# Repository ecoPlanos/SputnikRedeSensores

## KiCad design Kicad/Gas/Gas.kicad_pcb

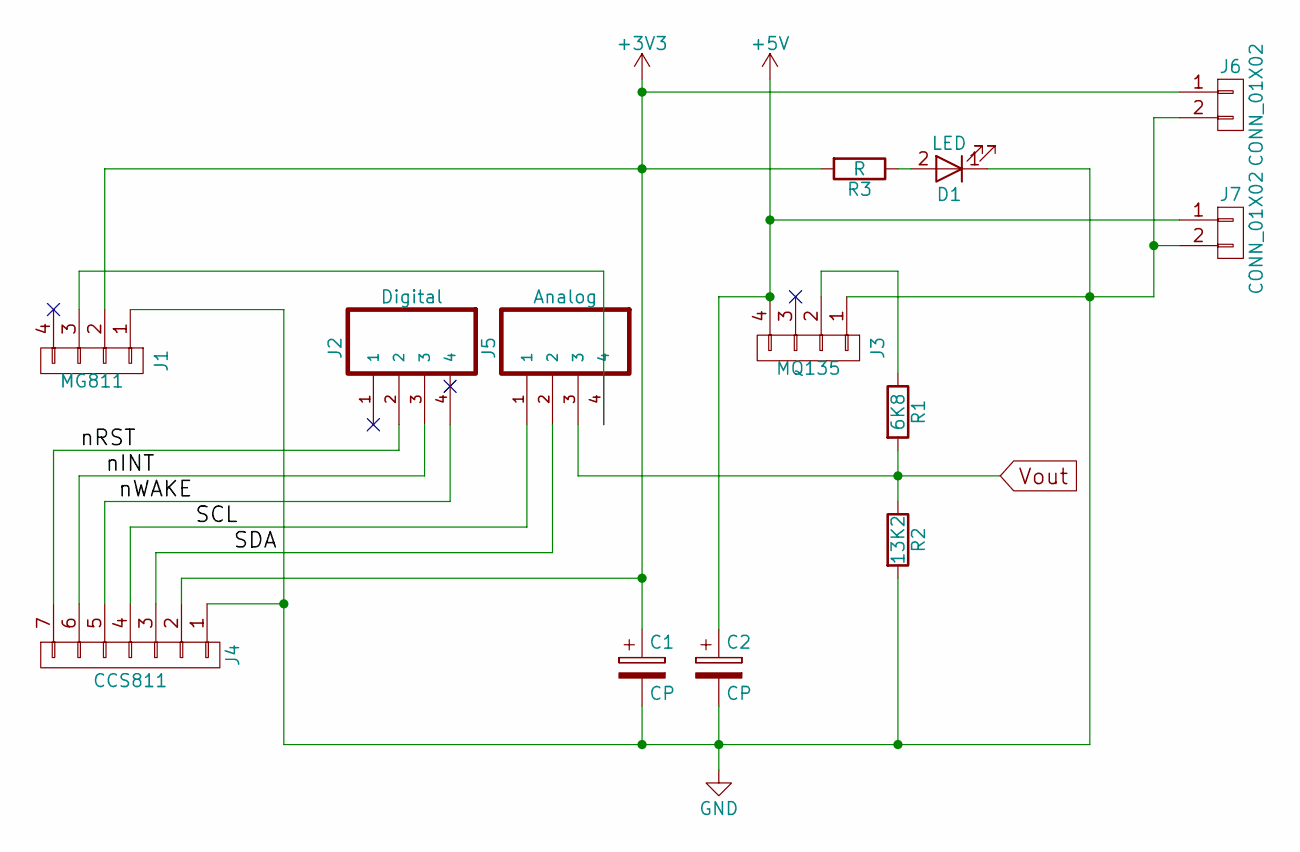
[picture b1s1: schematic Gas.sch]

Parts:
C1, C2: CP; CP_Radial_D5.0mm_P2.50mm
D1: LED; LED_D4.0mm
J1: MG811; Pin_Header_Straight_1x03_Pitch1.00mm
J2: Digital; JST_PHR-4
J3: MQ135; Pin_Header_Straight_1x04_Pitch2.54mm
J4: CCS811; Pin_Header_Straight_1x07_Pitch2.54mm
J5: Analog; JST_PHR-4
J6, J7: CONN_01X02; Socket_Strip_Angled_1x02_Pitch2.54mm
R1: 6K8; R_Axial_DIN0204_L3.6mm_D1.6mm_P5.08mm_Horizontal
R2: 13K2; R_Axial_DIN0204_L3.6mm_D1.6mm_P5.08mm_Horizontal
R3: R; R_Axial_DIN0204_L3.6mm_D1.6mm_P5.08mm_Horizontal

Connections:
+3V3: C1.1, J1.2, J4.2, J6.1, R3.2
+5V: C2.1, J3.4, J7.1
/SCL: J4.4, J5.1
/SDA: J4.3, J5.2
/nINT: J2.3, J4.6
/nRST: J2.2, J4.7
/nWAKE: J2.4, J4.5
GND: C1.2, C2.2, D1.1 (K), J1.1, J3.1, J4.1, J6.2, J7.2, R2.2
unnamed: D1.2 (A), R3.1
unnamed: J1.3, J5.4
unnamed: J3.2, R1.1
Vout: J5.3, R1.2, R2.1

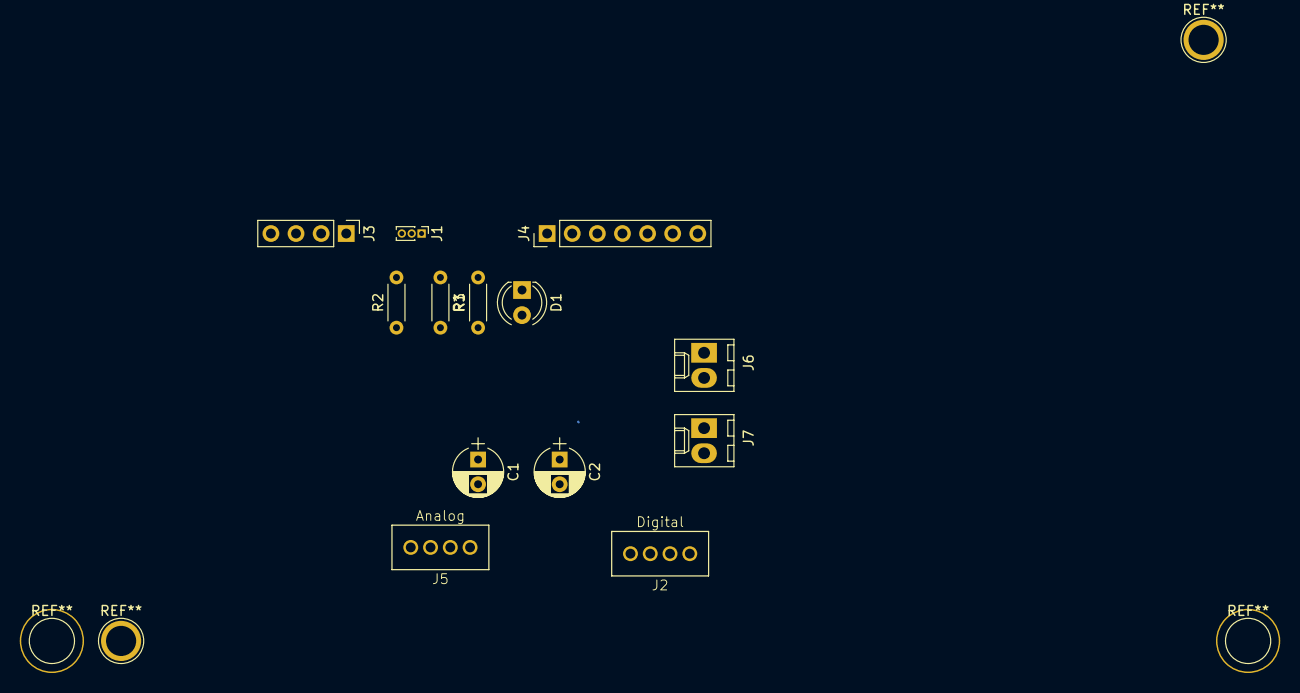
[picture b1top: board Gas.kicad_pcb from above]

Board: 2 copper layers, 13 parts (0 on the bottom side), 12 nets.

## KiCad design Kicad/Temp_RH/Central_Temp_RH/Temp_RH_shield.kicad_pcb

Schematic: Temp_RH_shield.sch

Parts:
C1: CP; CP_Radial_D6.3mm_P2.50mm
J1: Temp_RH_Module; TerminalBlock_Pheonix_PT-3.5mm_12pol
J2: micro_SD; Pin_Header_Straight_1x06_Pitch2.54mm
J3: RTC; Pin_Header_Straight_1x05_Pitch2.54mm
J4, J11: Screw_Terminal_1x02; TerminalBlock_Pheonix_PT-3.5mm_2pol
J5: MAX31855_HW; Pin_Header_Straight_1x06_Pitch2.54mm
J6: MAX31855_SW; Pin_Header_Straight_1x06_Pitch2.54mm
J12, J13, J14: CONN_01X01; Pin_Header_Straight_1x01_Pitch2.54mm
R1: 4650; R_Axial_DIN0309_L9.0mm_D3.2mm_P12.70mm_Horizontal
R2: 1779; R_Axial_DIN0309_L9.0mm_D3.2mm_P12.70mm_Horizontal
R3: 4630; R_Axial_DIN0309_L9.0mm_D3.2mm_P12.70mm_Horizontal
R4: 1787; R_Axial_DIN0309_L9.0mm_D3.2mm_P12.70mm_Horizontal
R5: 98.8; R_Axial_DIN0309_L9.0mm_D3.2mm_P12.70mm_Horizontal
R6: 9780; R_Axial_DIN0309_L9.0mm_D3.2mm_P12.70mm_Horizontal
R7: 178000; R_Axial_DIN0309_L9.0mm_D3.2mm_P12.70mm_Horizontal
R8: 180000; R_Axial_DIN0309_L9.0mm_D3.2mm_P12.70mm_Horizontal
SHIELD1: ARDUINO_DUE_SHIELD
SHIELD2: WIFI_SHIELD; ARDUINO_SHIELD
U1: LM324N; DIP-14_W7.62mm_Socket

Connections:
/DHT11_DATA: J1.1, SHIELD1.2
/DHT22_DATA: J1.2, SHIELD1.3
/NTC_AN: J1.7, SHIELD1.AD1
/PT100_AN: C1.1, R6.2, SHIELD1.AD0
/PT100_Red: J13.1, R1.1, R2.1
/PT100_Yellow: J14.1, R5.1
/RTC_CLK: J3.3, SHIELD1.48
/RTC_DATA: J3.2, SHIELD1.50
/RTC_RST: J3.1, SHIELD1.52
/SCL: J1.6, SHIELD1.21
/SDA: J1.5, SHIELD1.20
/SHT75_DATA: J1.4, SHIELD1.6
/SHT75_SCK: J1.3, SHIELD1.5
/uSD_CS: J2.4, SHIELD1.4
MAX31855_CS: J1.11, J5.1, J6.1, SHIELD1.10
MAX31855_GND: C1.2, J1.12, J2.2, J3.4, J4.1, J5.6, J6.6, J12.1, R7.2, SHIELD1.GND1, SHIELD1.GND2, SHIELD1.GND3, SHIELD1.GND4, SHIELD1.GND5, SHIELD2.GND1, SHIELD2.GND2, SHIELD2.GND3, U1.4
MAX31855_SCK_HW: J1.10, J2.5, J5.4, SHIELD1.SP3
MAX31855_SCK_SW: J6.4, SHIELD1.12
MAX31855_SO(MISO)_HW: J1.9, J2.6, J5.3, SHIELD1.SP1
MAX31855_SO(MISO)_SW: J6.3, SHIELD1.11
MAX31855_VCC: J3.5, J4.2, J5.5, SHIELD1.3V3
MAX31855_VCC_SW: J6.5, SHIELD1.13
unnamed: J2.1, R2.2, R4.1, SHIELD1.5V, SHIELD1.5V_4, SHIELD1.5V_5, SHIELD2.5V, U1.11
unnamed: J2.3, SHIELD1.SP4
unnamed: J11.1, SHIELD1.SDA1
unnamed: J11.2, SHIELD1.SCL1
unnamed: R1.2, R7.1, U1.3
unnamed: R3.1, R6.1, R8.1, U1.2
unnamed: R3.2, R4.2, R5.2
unnamed: R8.2, U1.1
unnamed: SHIELD1.18, SHIELD2.1
unnamed: SHIELD1.19, SHIELD2.0

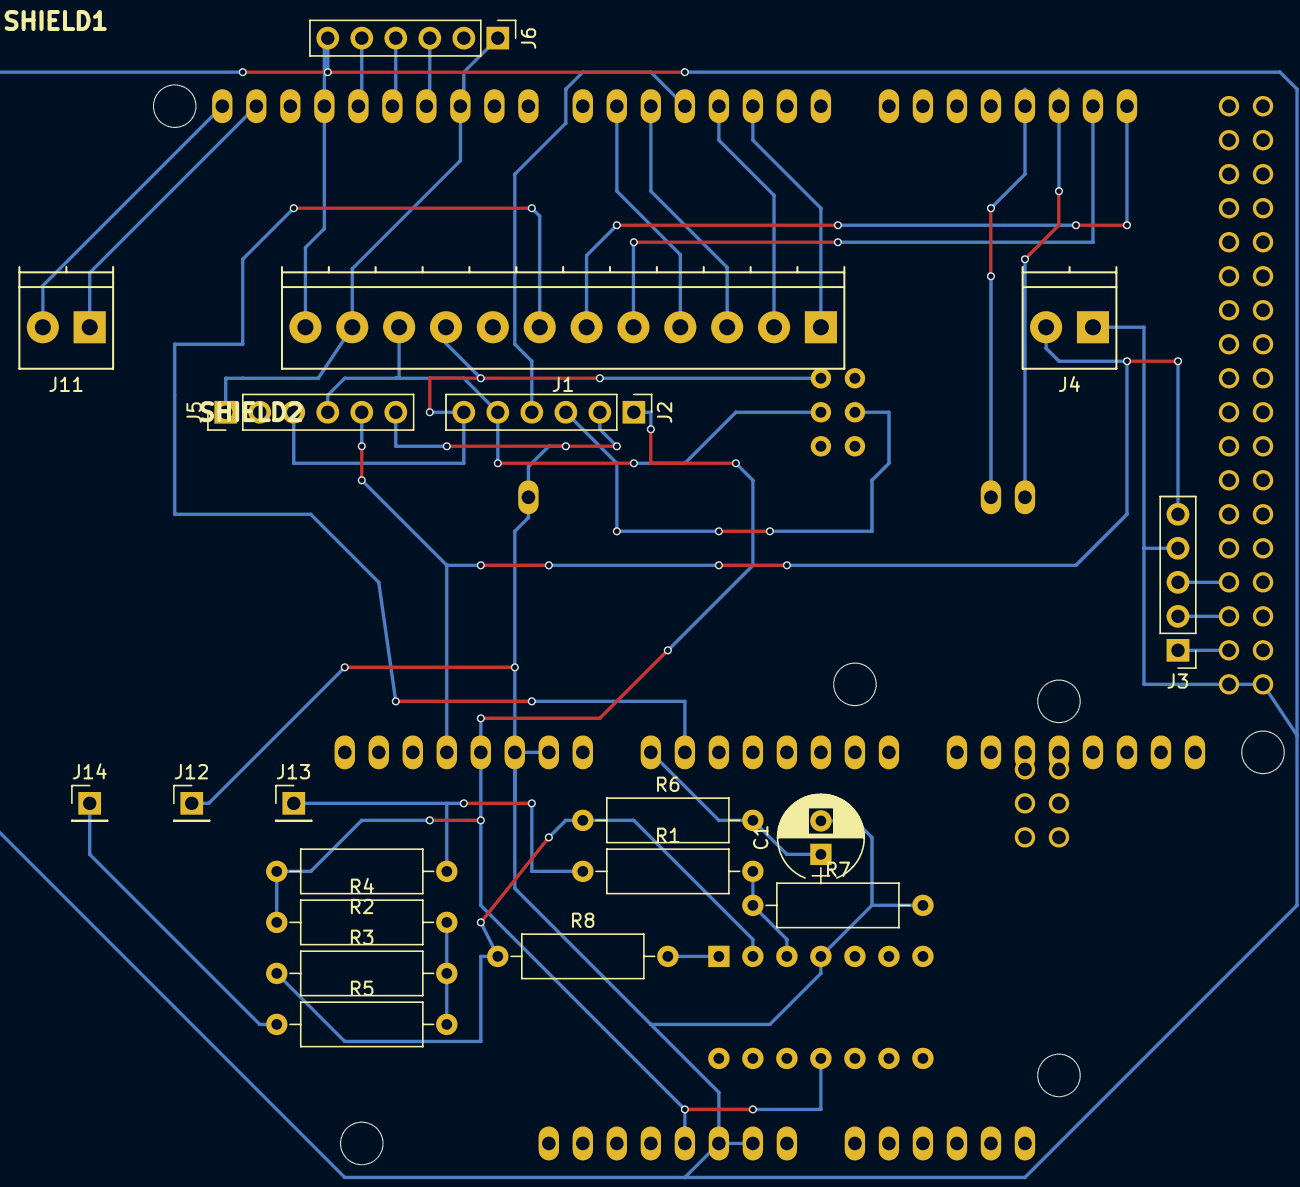
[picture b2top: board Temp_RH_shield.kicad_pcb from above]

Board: 2 copper layers, 22 parts (1 on the bottom side), 32 nets.

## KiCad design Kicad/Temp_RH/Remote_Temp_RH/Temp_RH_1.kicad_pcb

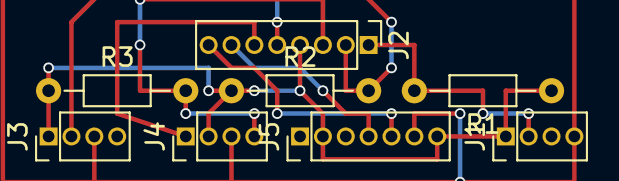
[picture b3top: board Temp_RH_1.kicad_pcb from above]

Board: 2 copper layers, 8 parts (0 on the bottom side), 8 nets.

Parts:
J1: DHT 11; Pin_Header_Straight_1x04_Pitch1.27mm
J2: Arduino; Pin_Header_Straight_1x08_Pitch1.27mm
J3: DHT 22; Pin_Header_Straight_1x04_Pitch1.27mm
J4: SHT 75; Pin_Header_Straight_1x04_Pitch1.27mm
J5: SHT 31; Pin_Header_Straight_1x07_Pitch1.27mm
R1, R2: R; R_Axial_DIN0204_L3.6mm_D1.6mm_P7.62mm_Horizontal
R3: 10K; R_Axial_DIN0204_L3.6mm_D1.6mm_P7.62mm_Horizontal

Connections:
+3V3: J1.1, J2.4, J3.1, J4.2, J5.2, J5.7, R1.1, R2.1, R3.1
/DataSHT75: J2.3, J4.4, R3.2
/Data_DHT11: J1.2, J2.1, R1.2
/SCL: J2.8, J5.5
/SDA: J2.7, J5.4
GND: J1.4, J2.5, J3.3, J4.3, J5.6
unnamed: J2.2, J3.2, R2.2
unnamed: J2.6, J4.1
